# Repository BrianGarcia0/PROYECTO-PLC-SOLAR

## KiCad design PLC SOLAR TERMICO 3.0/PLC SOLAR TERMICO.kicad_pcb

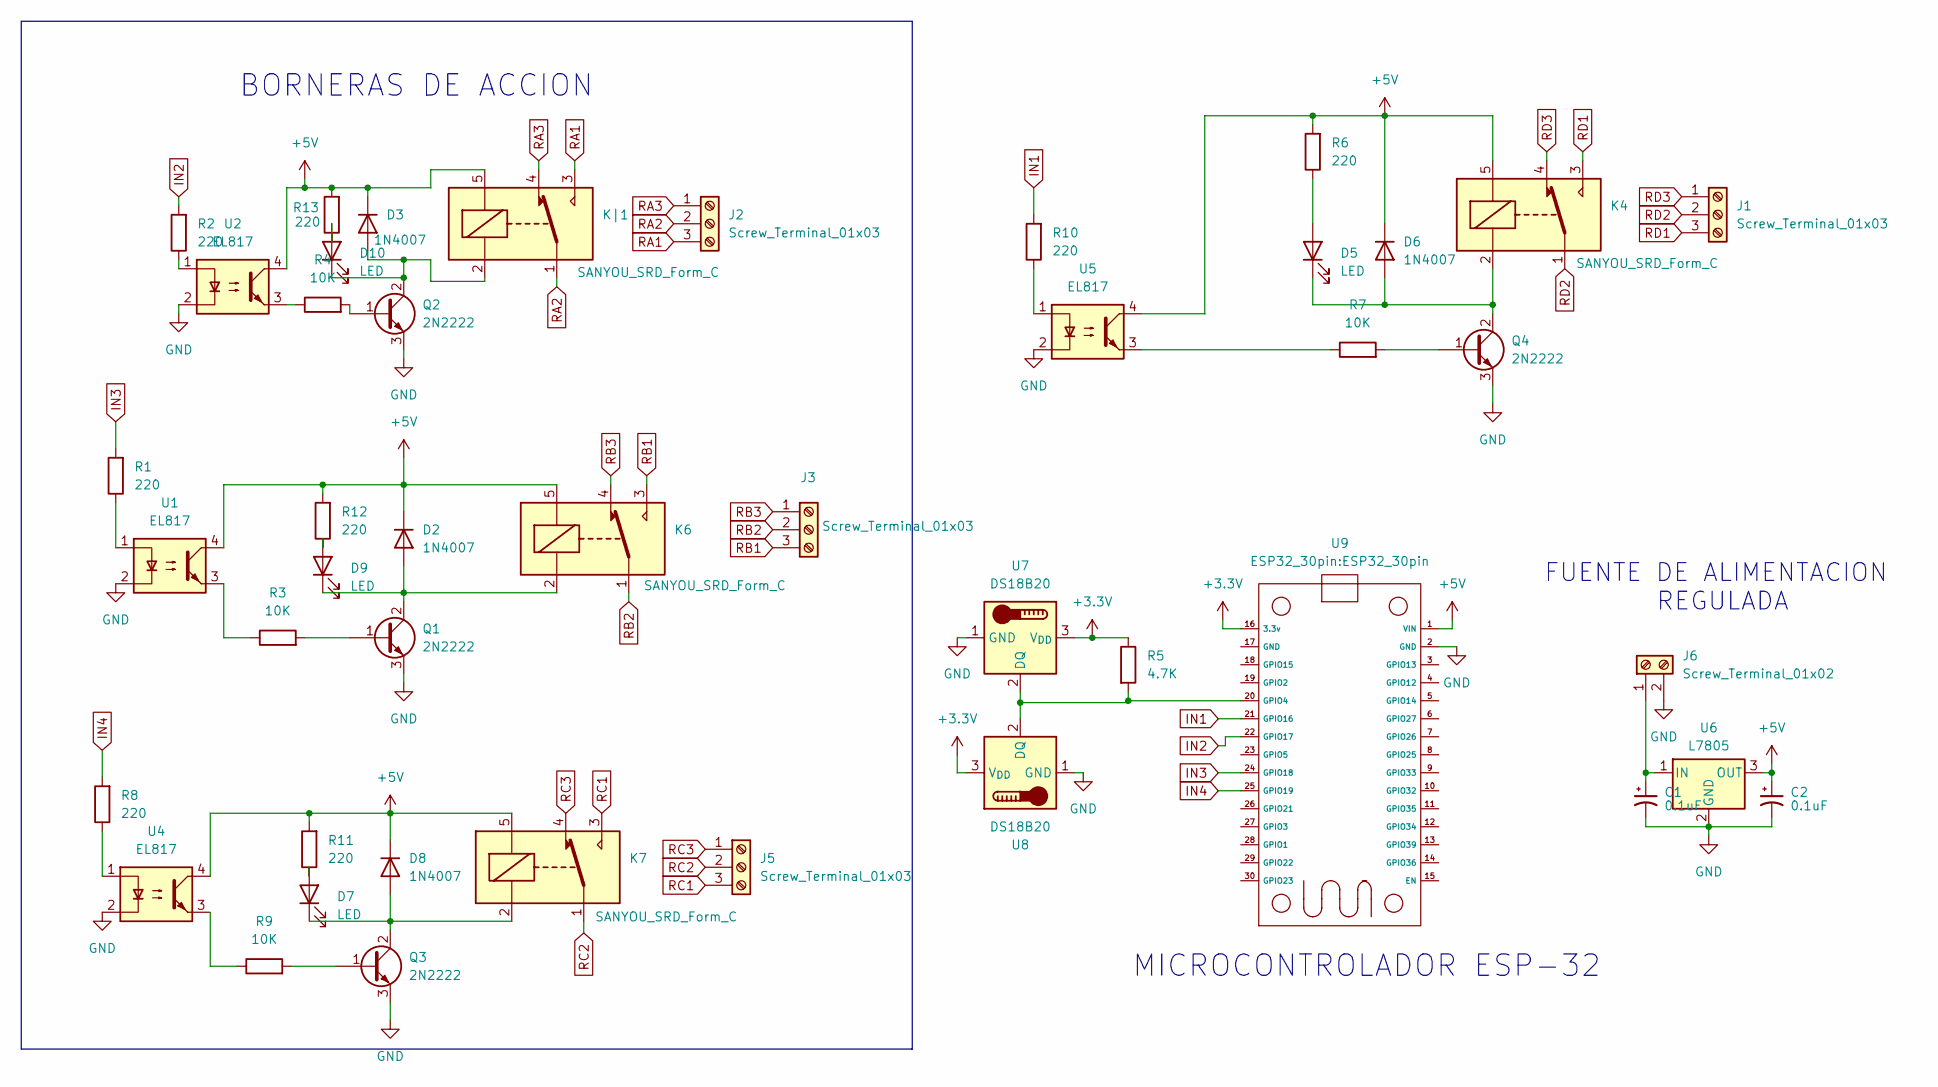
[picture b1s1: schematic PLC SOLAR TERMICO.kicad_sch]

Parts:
C1, C2: 0.1uF; CP_Elec_3x5.3
D2, D3, D6, D8: 1N4007; D_SMA
D5, D7, D9, D10: LED; LED_0603_1608Metric
J1, J2, J3, J5: Screw_Terminal_01x03; TerminalBlock_Phoenix_MKDS-1,5-3-5.08_1x03_P5.08mm_Horizont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
J6: Screw_Terminal_01x02; TerminalBlock_Philmore_TB132_1x02_P5.00mm_Horizontal
K4, K6, K7: SANYOU_SRD_Form_C; Relay_SPDT_SANYOU_SRD_Series_Form_C
K|1: SANYOU_SRD_Form_C; Relay_SPDT_SANYOU_SRD_Series_Form_C
Q1, Q2, Q3, Q4: 2N2222; SOT-23
R1, R2, R6, R8, R10, R11, R12, R13: 220; R_0805_2012Metric
R3, R4, R7, R9: 10K; R_0805_2012Metric
R5: 4.7K; R_0805_2012Metric
U1, U2, U4, U5: EL817; DIP-4_W7.62mm
U6: L7805; TO-263-2
U7, U8: DS18B20; TO-92_Inline
U9: ESP32_30pin

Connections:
+3.3V: R5.1, U7.3 (V_{DD}), U8.3 (V_{DD}), U9.16 (3.3v)
+5V: C2.1, D2.1 (K), D3.1 (K), D6.1 (K), D8.1 (K), K4.5, K6.5, K7.5, K|1.5, R6.2, R11.2, R12.2, R13.2, U1.4, U2.4, U4.4, U5.4, U6.3 (OUT), U9.1 (VIN)
GND: C1.2, C2.2, J6.2, Q1.3 (E), Q2.3 (E), Q3.3 (E), Q4.3 (E), U1.2, U2.2, U4.2, U5.2, U6.2 (GND), U7.1 (GND), U8.1 (GND), U9.2 (GND)
IN1: R10.2, U9.21 (GPIO16)
IN2: R2.2, U9.22 (GPIO17)
IN3: R1.2, U9.24 (GPIO18)
IN4: R8.2, U9.25 (GPIO19)
unnamed: D2.2 (A), D9.1 (K), K6.2, Q1.2 (C)
unnamed: D5.2 (A), R6.1
unnamed: D5.1 (K), D6.2 (A), K4.2, Q4.2 (C)
unnamed: D7.2 (A), R11.1
unnamed: D7.1 (K), D8.2 (A), K7.2, Q3.2 (C)
unnamed: D9.2 (A), R12.1
unnamed: D10.2 (A), R13.1
unnamed: D3.2 (A), D10.1 (K), K|1.2, Q2.2 (C)
unnamed: C1.1, J6.1, U6.1 (IN)
unnamed: Q1.1 (B), R3.2
unnamed: Q2.1 (B), R4.2
unnamed: Q3.1 (B), R9.2
unnamed: Q4.1 (B), R7.2
unnamed: R1.1, U1.1
unnamed: R2.1, U2.1
unnamed: R3.1, U1.3
unnamed: R4.1, U2.3
unnamed: R7.1, U5.3
unnamed: R8.1, U4.1
unnamed: R9.1, U4.3
unnamed: R10.1, U5.1
unnamed: R5.2, U7.2 (DQ), U8.2 (DQ), U9.20 (GPIO4)
RA1: J2.3, K|1.3
RA2: J2.2, K|1.1
RA3: J2.1, K|1.4
RB1: J3.3, K6.3
RB2: J3.2, K6.1
RB3: J3.1, K6.4
RC1: J5.3, K7.3
RC2: J5.2, K7.1
RC3: J5.1, K7.4
RD1: J1.3, K4.3
RD2: J1.2, K4.1
RD3: J1.1, K4.4

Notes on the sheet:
FUENTE DE ALIMENTACION REGULADA
BORNERAS DE ACCION
MICROCONTROLADOR ESP-32

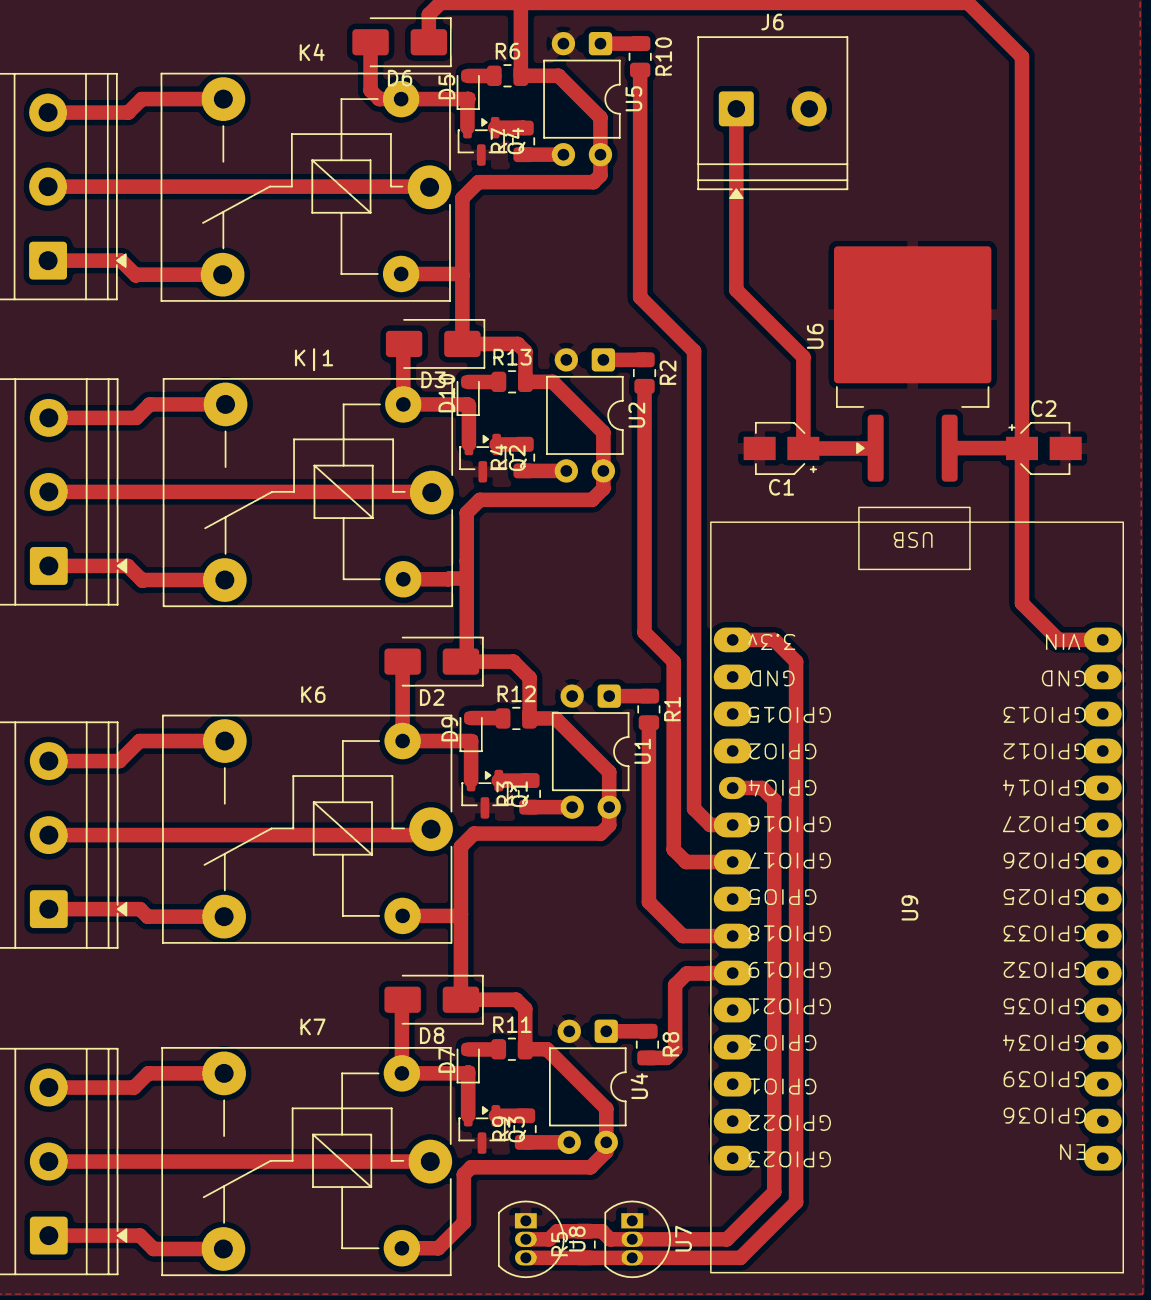
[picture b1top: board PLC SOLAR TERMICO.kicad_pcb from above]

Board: 2 copper layers, 44 parts (0 on the bottom side), 41 nets.
